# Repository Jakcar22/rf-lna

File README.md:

# 915 MHz GaAs MMIC Low Noise Amplifier (LNA) PCB

A 915 MHz low-noise amplifier printed circuit board built around a Qorvo GaAs pHEMT MMIC, designed as part of a self-directed RF hardware project targeting aerospace and defense applications.

## Project Summary

This project takes a commercial GaAs MMIC LNA and builds a complete RF front-end PCB around it: bias network, supply filtering, DC blocking, and 50 Ω microstrip routing. The goal is end-to-end ownership of an RF design from datasheet study through KiCAD layout, simulation, fabrication, and VNA validation.

**Version 1 (in this repository):** Built around the **Qorvo SPF5189Z** GaAs MMIC LNA. KiCAD layout complete (DRC clean, ERC clean). LTspice bias and supply-filter simulations complete.

**Version 2 (planned):** Migration to the **Qorvo SPF5043Z** GaAs MMIC LNA. The SPF5043Z draws 46 mA versus the SPF5189Z's 90 mA, offering better power efficiency at modest cost in gain. Footprint swap (SOT-363 to SOT-343), trace re-route, and bias network re-simulation are planned.

## Design Goals

- **Target Frequency:** 915 MHz (ISM band)
- **Substrate:** FR4 (εr ≈ 4.4), 1.6 mm thickness
- **System Impedance:** 50 Ω
- **Target Performance (per SPF5189Z datasheet):**
  - Gain (S21): ~19 to 20 dB at 915 MHz
  - Noise Figure: ~0.6 dB
  - Supply: 5 V at ~90 mA
  - Output P1dB: ~22 to 23 dBm

## Circuit Architecture

The SPF5189Z has integrated internal impedance matching, so the external circuit is minimal:

```
RF IN --[C2 100 pF block]--[L1 1.5 nH match]-- Pin 1 (RF IN)
                                                  |
                                              SPF5189Z
                                                  |
Pin 3 (RF OUT / DC BIAS) --[C3 100 pF block]-- RF OUT
        |
   [L2 150 nH RF choke]
        |
   [C4 100 pF + C1 100 nF bypass]
        |
      5 V supply

Pin 2, Pin 4 -> GND (with via stitching directly at chip)
```

**Pin 3 dual purpose:** Pin 3 is both the RF output AND the DC bias input for VDD. The 150 nH inductor acts as an RF choke (passes DC, blocks 915 MHz). The 100 pF cap on the output passes RF while blocking the supply DC from reaching the load.

## Bill of Materials

| Reference | Value | Function |
|---|---|---|
| U1 | SPF5189Z | GaAs MMIC LNA |
| C1 | 100 nF (0.1 µF) | VDD bypass (bulk) |
| C2, C3, C4 | 100 pF | DC blocks on RF input, RF output, VDD |
| L1 | 1.5 nH | Input matching inductor |
| L2 | 150 nH | VDD RF choke |
| J1, J2 | SMA Edge Mount | RF input/output connectors |
| J3 | 1x2 header | 5 V power input |

## Tools Used

- **KiCAD 9.0** — Schematic capture and PCB layout
- **LTspice** — DC operating point and AC sweep simulation
- **Keysight ADS** — S-parameter and noise-figure simulation (planned, via Purdue ECN)
- **OSHPark** — PCB fabrication (planned)
- **VNA** — S11 and S21 validation (planned post-fabrication)

## Board Specifications

- **Layers:** 2-layer FR4
- **Thickness:** 1.6 mm
- **Trace Width:** 3.0 mm for 50 Ω microstrip on FR4 1.6 mm
- **Layout Rules:**
  - RF traces kept short and direct between SMA and chip
  - Ground stitching vias placed around RF traces
  - Power supply traces routed away from RF signal path
  - Via holes placed adjacent to GND pins to minimize inductance
- **DRC:** Clean (0 violations, 0 unconnected items)
- **ERC:** Clean (0 violations)

## Simulation Results

### LTspice: Supply-Rail Isolation (AC Sweep)

Verified that the L2 RF choke and C1 bypass capacitor prevent the 915 MHz RF signal from coupling back into the supply line. AC sweep from 1 MHz to 4 GHz, with 1 V AC source representing the worst-case RF leakage into the supply node.

| Frequency | Attenuation at VDD Node |
|---|---|
| 50 MHz | approximately -64 dB |
| **915 MHz** | **approximately -114 dB** |
| 4 GHz | approximately -144 dB |

**Result:** The supply filter provides approximately 114 dB of RF isolation at the operating frequency. RF signal cannot meaningfully couple back into the power supply, so the bias circuit is stable.

### LTspice: DC Operating Point

Modeled with V1 = 5 V DC, L2 = 150 nH, R1 = 55.6 Ω (SPF5189Z equivalent chip resistance at 90 mA), C1 = 100 nF bypass.

| Node / Component | Simulated | Expected | Status |
|---|---|---|---|
| V(n001) — VDD node | 5.000 V | 5 V | Pass |
| V(n002) — after RF choke | 4.99991 V | ~5 V | Pass |
| I(R1) — chip bias current | 89.9 mA | ~90 mA | Pass |
| I(L2) — choke current | 89.9 mA | ~90 mA | Pass |
| I(C1) — bypass cap current | ~0 A | 0 A (open at DC) | Pass |

**Result:** DC bias network delivers 5 V at 90 mA to the chip as specified in the SPF5189Z datasheet.

### Keysight ADS: S-Parameter and Noise-Figure Analysis (Pending)

Planned simulations once the Touchstone (.s2p) model is loaded into ADS via Purdue ECN:

- S21 (gain) vs frequency, with markers at 915 MHz
- Noise Figure (NF) and NFmin vs frequency
- S11, S22 vs frequency (log-magnitude and Smith Chart)
- P1dB (output 1 dB compression point)
- Stability factors K and B1 vs frequency

ADS simulation files and output plots are not included in this repository.

## Validation Plan (Post-Fabrication)

1. Visually inspect solder joints under magnification
2. Measure DC operating point with bench DMM (verify 5 V supply, ~90 mA current for SPF5189Z)
3. Connect to VNA and measure:
   - S11 (input return loss) — target dip below -10 dB at 915 MHz
   - S21 (gain) — target ~19 to 20 dB at 915 MHz
   - S22 (output return loss) — target below -10 dB
4. Compare measured S-parameters against simulation results
5. Document any discrepancies and root-cause them

## Project Status

- [x] Theory reading and reference application circuit studied
- [x] BOM finalized for SPF5189Z
- [x] LTspice DC operating point simulation (5 V at 89.9 mA confirmed)
- [x] LTspice AC sweep supply filter performance (~114 dB isolation at 915 MHz)
- [x] KiCAD schematic capture (ERC clean)
- [x] KiCAD PCB layout (DRC clean)
- [ ] Gerber export
- [ ] PCB ordered from OSHPark
- [ ] Keysight ADS S-parameter simulation
- [ ] Board assembled and DC operating point measured
- [ ] VNA measurements (S11, S21, S22) taken
- [ ] Simulation vs measured comparison documented
- [ ] v2 migration to SPF5043Z (footprint swap, re-route, bias re-simulation)

## References

- [Qorvo SPF5189Z Datasheet (Mouser)](https://www.mouser.com/datasheet/2/412/RFMDS04436_1-2564742.pdf)
- [Qorvo SPF5043Z Product Page (DigiKey)](https://www.digikey.com/en/products/detail/qorvo/SPF5043Z/2708620)
- *Microwave Engineering* — David M. Pozar
- *RF Circuit Design* — Christopher Bowick

## License

Hardware design files (schematics, PCB layouts, BOM, Gerbers) are released under the **CERN Open Hardware License Version 2 - Permissive (CERN-OHL-P)**. Software and documentation are released under the **MIT License**.

---

*Project in active development. Boards not yet fabricated. Measurements not yet taken. README will be updated as milestones complete.*

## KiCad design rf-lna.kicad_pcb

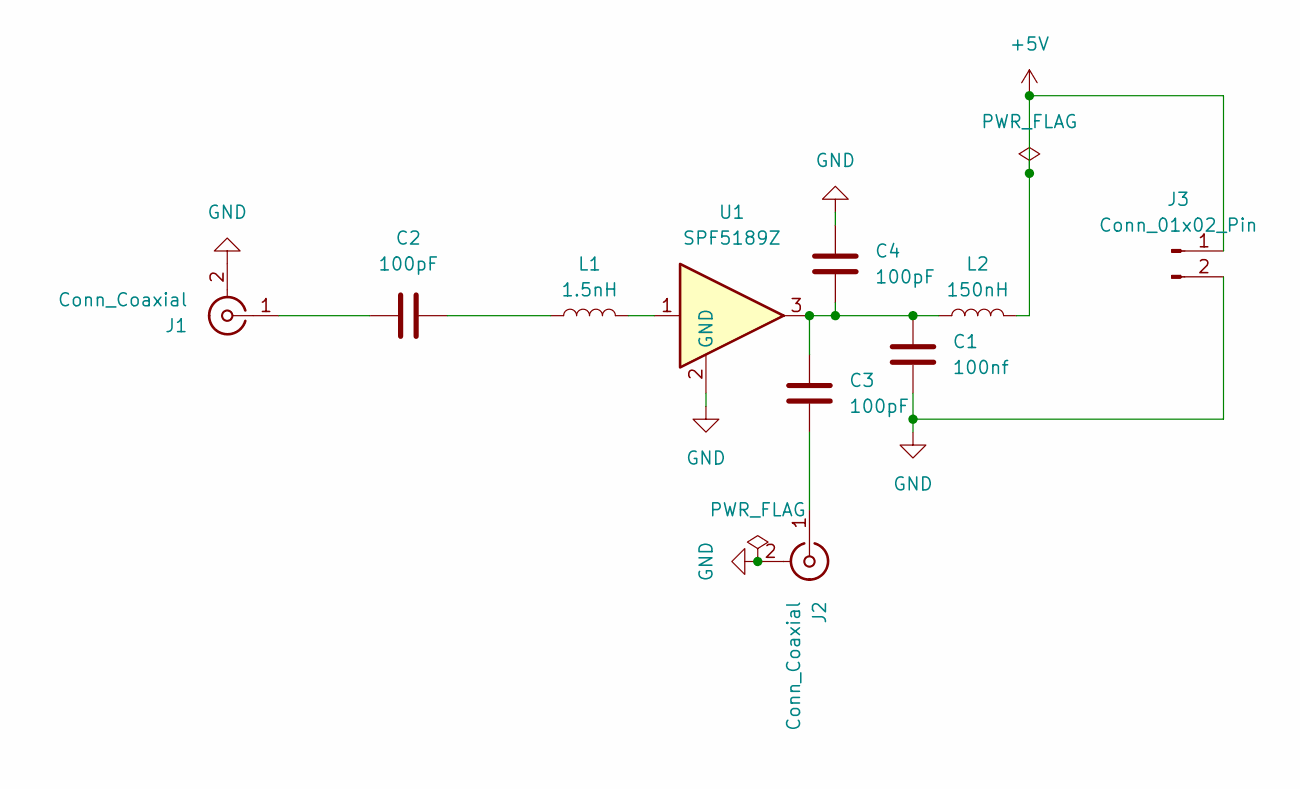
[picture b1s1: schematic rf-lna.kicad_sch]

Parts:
C1: 100nf; C_0402_1005Metric_Pad0.74x0.62mm_HandSolder
C2, C3, C4: 100pF; C_0402_1005Metric_Pad0.74x0.62mm_HandSolder
J1, J2: Conn_Coaxial; SMA_Samtec_SMA-J-P-H-ST-EM1_EdgeMount
J3: Conn_01x02_Pin; PinHeader_1x02_P2.54mm_Vertical
L1: 1.5nH; L_0603_1608Metric_Pad1.05x0.95mm_HandSolder
L2: 150nH; L_0603_1608Metric_Pad1.05x0.95mm_HandSolder
U1: SPF5189Z; SOT-363_SC-70-6_Handsoldering

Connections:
+5V: J3.1, L2.2
GND: C1.2, C4.1, J1.2 (Ext), J2.2 (Ext), J3.2, U1.2 (GND), U1.4, U1.5, U1.6
unnamed: C1.1, C3.1, C4.2, L2.1, U1.3
unnamed: C2.2, L1.1
unnamed: C2.1, J1.1 (In)
unnamed: C3.2, J2.1 (In)
unnamed: L1.2, U1.1

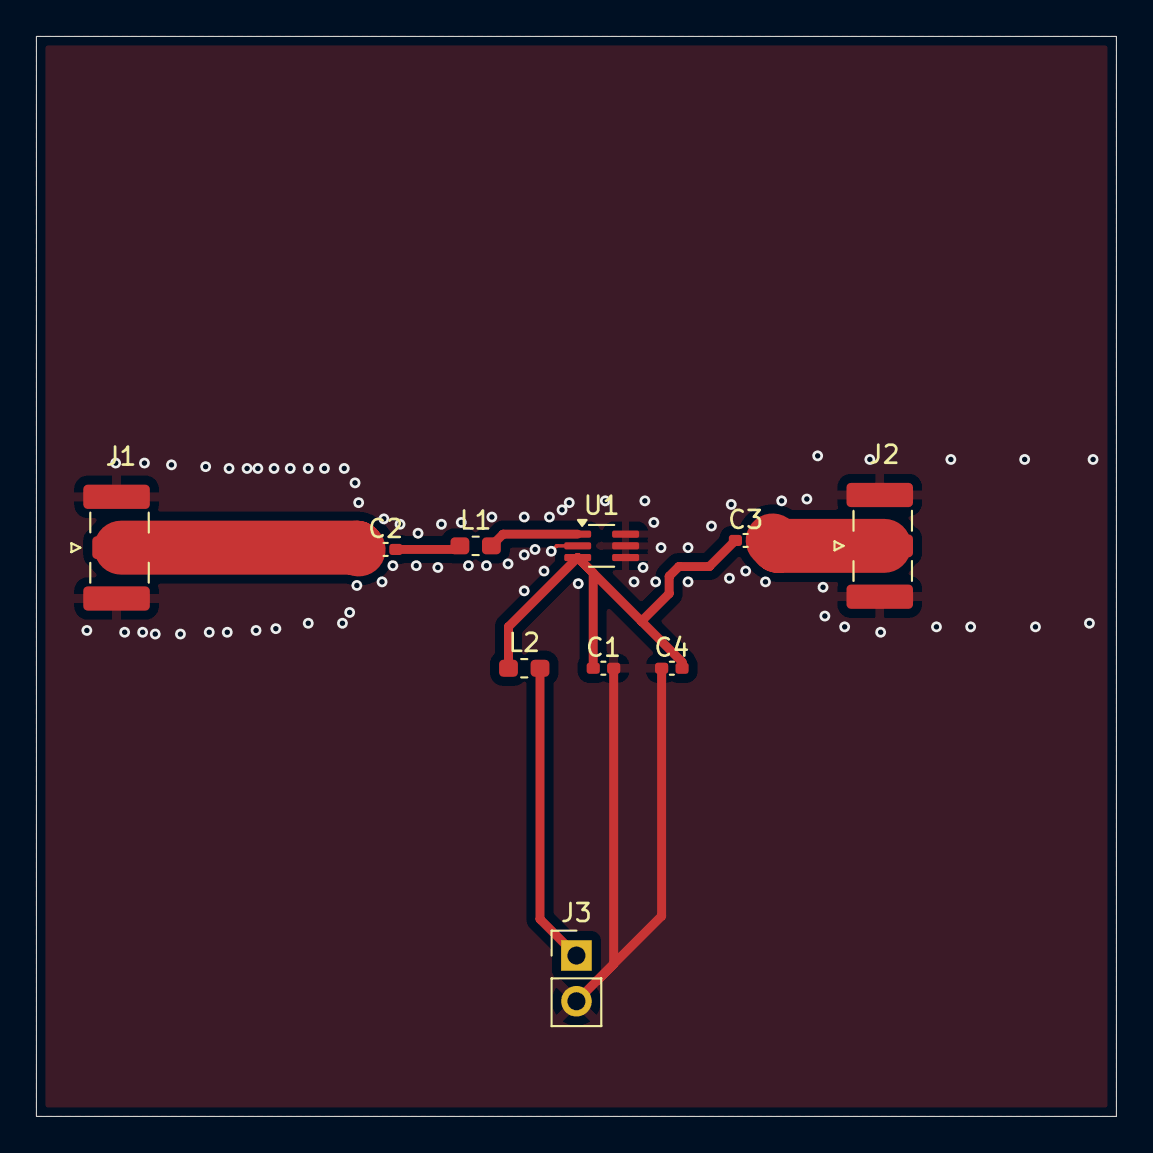
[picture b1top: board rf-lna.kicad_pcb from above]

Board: 2 copper layers, 60.0 x 60.0 mm, 10 parts (0 on the bottom side), 7 nets.

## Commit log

2026-05-29 Revise README for comprehensive project documentation
    Expanded the README to include detailed project description, design goals, circuit architecture, bill of materials, tools used, board specifications, simulation results, validation plan, project stat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
2026-05-29 Add KiCAD project files (SPF5189Z v1)
2026-05-29 Add LTspice simulation files and verification screenshots
2026-05-29 Revise README for SPF5189Z integration and updates
    Updated project details and specifications to reflect the change from SPF5043Z to SPF5189Z. Adjusted performance targets and validation plans accordingly.
